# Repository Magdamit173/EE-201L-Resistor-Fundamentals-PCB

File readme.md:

### EE-201L-Resistor-Fundamentals-PCB

- Self Explanatory Repository ~ Cheers!

<br>

<center> <h3> Schematic </h3> </center>

<center> <h3> 3D View </h3> </center>

<center> <h3> Back/Bottom Copper</h3> </center>

<center> <h3> Front/Top Silkscreen</h3> </center>

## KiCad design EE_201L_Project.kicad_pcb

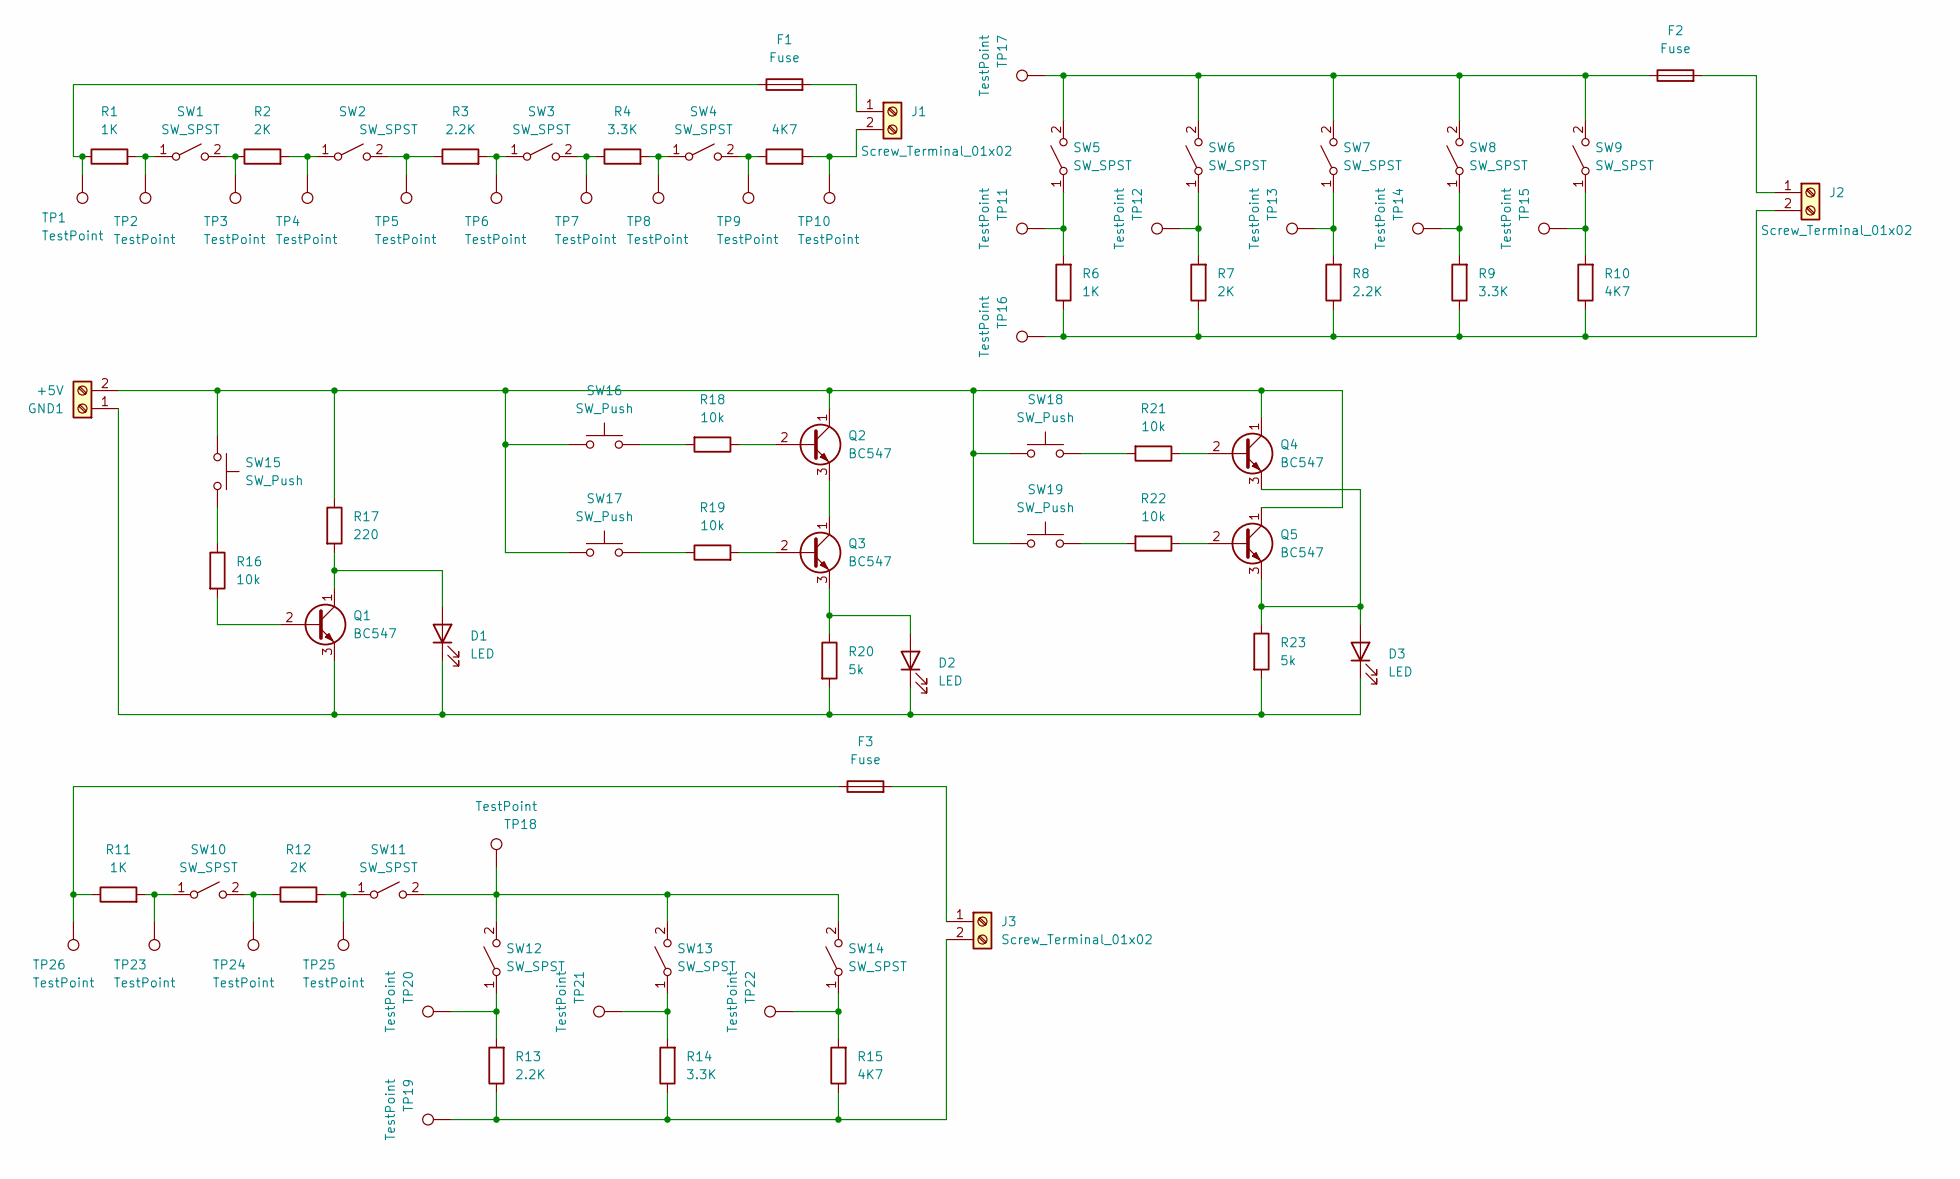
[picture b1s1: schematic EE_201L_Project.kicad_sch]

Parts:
D1, D2, D3: LED; LED_D5.0mm
F1, F2, F3: Fuse; Fuseholder_Cylinder-5x20mm_Schurter_0031_8201_Horizontal_Op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
GND1: +5V; TerminalBlock_Phoenix_MKDS-1,5-2_1x02_P5.00mm_Horizontal
J1, J2, J3: Screw_Terminal_01x02; TerminalBlock_Phoenix_MKDS-1,5-2-5.08_1x02_P5.08mm_Horizont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
Q1, Q2, Q3, Q4, Q5: BC547; TO-92_Inline
R1, R6, R11: 1K; R_Axial_DIN0207_L6.3mm_D2.5mm_P7.62mm_Horizontal_2.00_Diame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
R2, R7, R12: 2K; R_Axial_DIN0207_L6.3mm_D2.5mm_P7.62mm_Horizontal_2.00_Diame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
R3, R8, R13: 2.2K; R_Axial_DIN0207_L6.3mm_D2.5mm_P7.62mm_Horizontal_2.00_Diame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
R4, R9, R14: 3.3K; R_Axial_DIN0207_L6.3mm_D2.5mm_P7.62mm_Horizontal_2.00_Diame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
R5, R10, R15: 4K7; R_Axial_DIN0207_L6.3mm_D2.5mm_P7.62mm_Horizontal_2.00_Diame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
R16, R18, R19, R21, R22: 10k; R_Axial_DIN0207_L6.3mm_D2.5mm_P7.62mm_Horizontal_2.00_Diame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
R17: 220; R_Axial_DIN0207_L6.3mm_D2.5mm_P7.62mm_Horizontal_2.00_Diame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
R20, R23: 5k; R_Axial_DIN0207_L6.3mm_D2.5mm_P7.62mm_Horizontal_2.00_Diame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
SW1, SW2, SW3, SW4, SW5, SW6, SW7, SW8, SW9, SW10, SW11, SW12, SW13, SW14: SW_SPST; SW_CK_JS202011CQN_DPDT_Straight_Enhance
SW15, SW16, SW17, SW18, SW19: SW_Push; SW_PUSH_6mm_H8mm
TP1, TP2, TP3, TP4, TP5, TP6, TP7, TP8, TP9, TP10, TP11, TP12, TP13, TP14, TP15, TP16, TP17, TP18, TP19, TP20, TP21, TP22, TP23, TP24, TP25, TP26: TestPoint; TestPoint_Bridge_Pitch2.54mm_Drill1.0mm

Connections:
unnamed: D1.2 (A), Q1.1 (C), R17.2
unnamed: D1.1 (K), D2.1 (K), D3.1 (K), GND1.1, Q1.3 (E), R20.2, R23.2
unnamed: D2.2 (A), Q3.3 (E), R20.1
unnamed: D3.2 (A), Q4.3 (E), Q5.3 (E), R23.1
unnamed: F1.1, R1.1, TP1.1
unnamed: F3.1, R11.1, TP26.1
unnamed: GND1.2, Q2.1 (C), Q4.1 (C), Q5.1 (C), R17.1, SW15.1, SW16.1, SW17.1, SW18.1, SW19.1
unnamed: F1.2, J1.1
unnamed: J1.2, R5.2, TP10.1
unnamed: F2.2, J2.1
unnamed: J2.2, R6.1, R7.1, R8.1, R9.1, R10.1, TP16.1
unnamed: F3.2, J3.1
unnamed: J3.2, R13.1, R14.1, R15.1, TP19.1
unnamed: Q1.2 (B), R16.2
unnamed: Q2.2 (B), R18.1
unnamed: Q2.3 (E), Q3.1 (C)
unnamed: Q3.2 (B), R19.2
unnamed: Q4.2 (B), R21.1
unnamed: Q5.2 (B), R22.1
unnamed: R16.1, SW15.2
unnamed: R18.2, SW16.2
unnamed: R19.1, SW17.2
unnamed: R21.2, SW18.2
unnamed: R22.2, SW19.2
unnamed: R1.2, SW1.1 (A), TP2.1
unnamed: R2.1, SW1.2 (B), TP3.1
unnamed: R2.2, SW2.1 (A), TP4.1
unnamed: R3.1, SW2.2 (B), TP5.1
unnamed: R3.2, SW3.1 (A), TP6.1
unnamed: R4.1, SW3.2 (B), TP7.1
unnamed: R4.2, SW4.1 (A), TP8.1
unnamed: R5.1, SW4.2 (B), TP9.1
unnamed: R6.2, SW5.1 (A), TP11.1
unnamed: F2.1, SW5.2 (B), SW6.2 (B), SW7.2 (B), SW8.2 (B), SW9.2 (B), TP17.1
unnamed: R7.2, SW6.1 (A), TP12.1
unnamed: R8.2, SW7.1 (A), TP13.1
unnamed: R9.2, SW8.1 (A), TP14.1
unnamed: R10.2, SW9.1 (A), TP15.1
unnamed: R11.2, SW10.1 (A), TP23.1
unnamed: R12.1, SW10.2 (B), TP24.1
unnamed: R12.2, SW11.1 (A), TP25.1
unnamed: SW11.2 (B), SW12.2 (B), SW13.2 (B), SW14.2 (B), TP18.1
unnamed: R13.2, SW12.1 (A), TP20.1
unnamed: R14.2, SW13.1 (A), TP21.1
unnamed: R15.2, SW14.1 (A), TP22.1

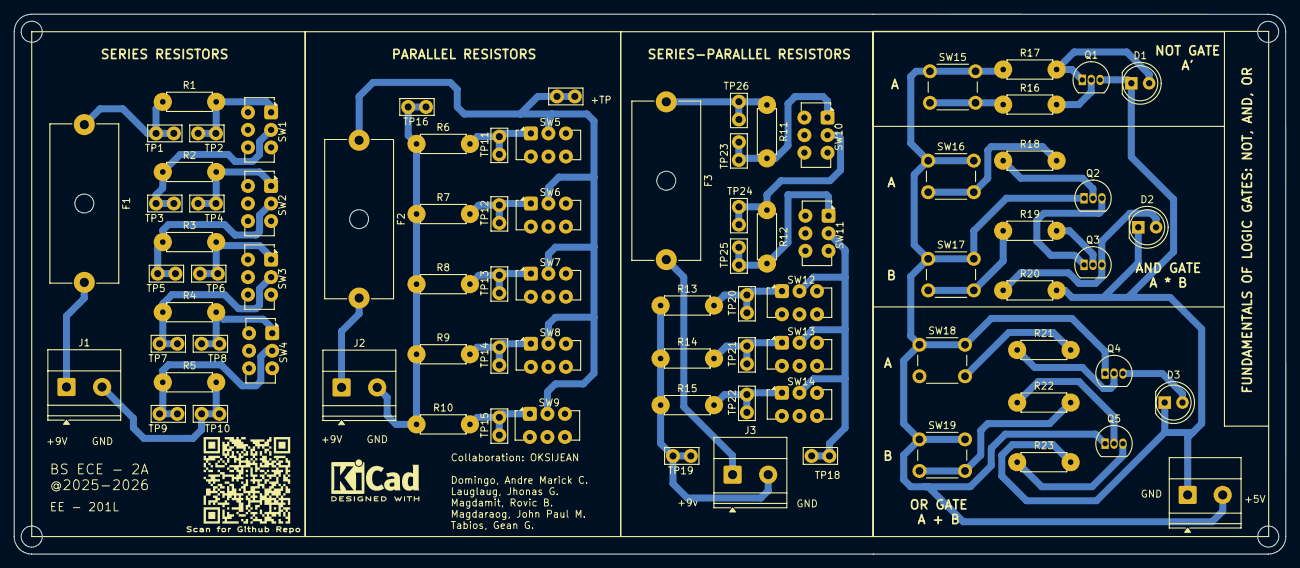
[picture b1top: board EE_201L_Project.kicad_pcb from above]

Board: 2 copper layers, 181.4 x 77.0 mm, 84 parts (0 on the bottom side), 45 nets.

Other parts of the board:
Scan for Github Repo: LOGO; qr_v2

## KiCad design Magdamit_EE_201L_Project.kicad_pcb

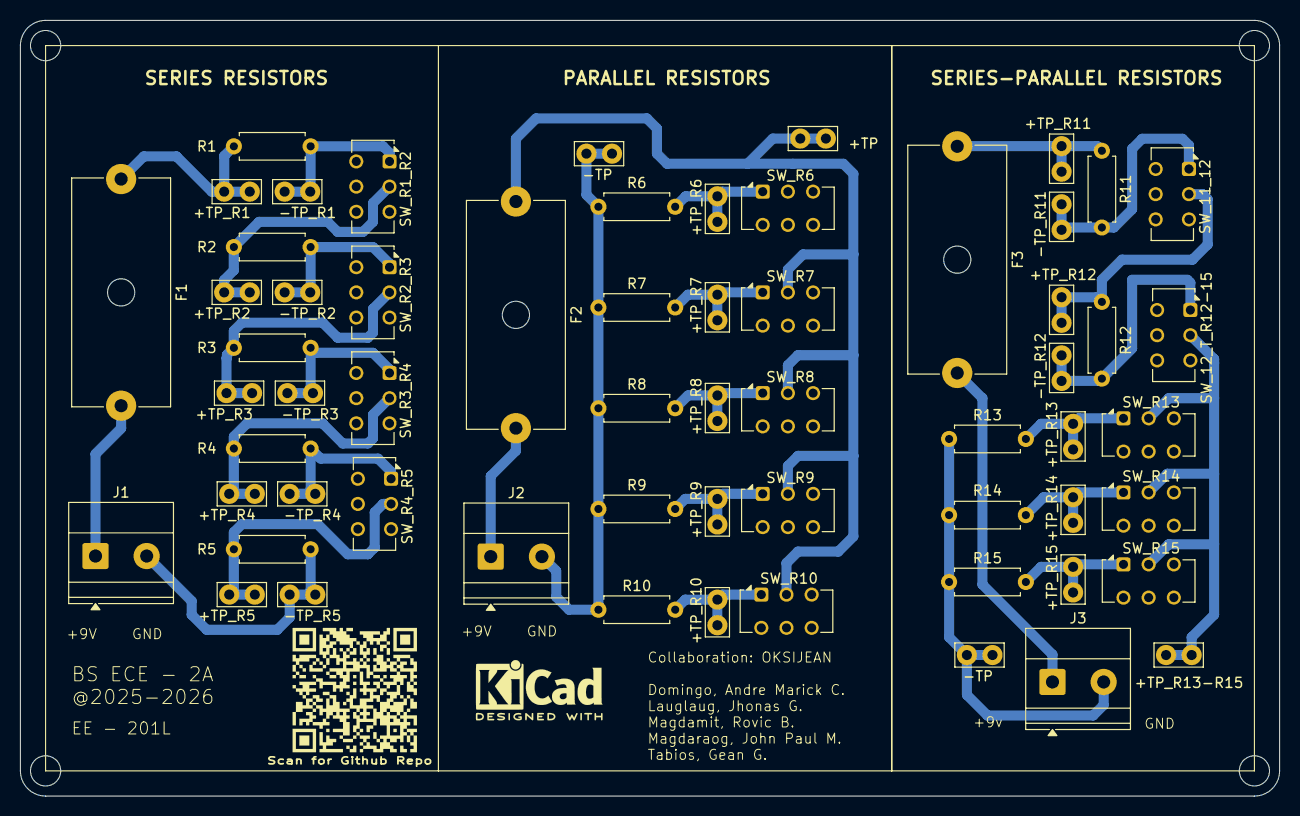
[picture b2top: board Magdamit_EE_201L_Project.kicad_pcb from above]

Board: 2 copper layers, 125.0 x 77.0 mm, 62 parts (0 on the bottom side), 29 nets.

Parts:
+TP_R1, +TP_R2, +TP_R3, +TP_R4, +TP_R5, +TP_R6, +TP_R7, +TP_R8, +TP_R9, +TP_R10, +TP_R11, +TP_R12, +TP_R13, +TP_R13-R15, +TP_R14, +TP_R15: TestPoint; TestPoint_Bridge_Pitch2.54mm_Drill1.0mm
-TP: TestPoint; TestPoint_Bridge_Pitch2.54mm_Drill1.0mm
-TP#2: TestPoint; TestPoint_Bridge_Pitch2.54mm_Drill1.0mm
-TP_R1, -TP_R2, -TP_R3, -TP_R4, -TP_R5, -TP_R11, -TP_R12: TestPoint; TestPoint_Bridge_Pitch2.54mm_Drill1.0mm
F1, F2, F3: Fuse; Fuseholder_Cylinder-5x20mm_Schurter_0031_8201_Horizontal_Op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
J1, J2, J3: Screw_Terminal_01x02; TerminalBlock_Phoenix_MKDS-1,5-2-5.08_1x02_P5.08mm_Horizont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
R1, R6, R11: 330R; R_Axial_DIN0207_L6.3mm_D2.5mm_P7.62mm_Horizontal
R2, R7, R12: 470R; R_Axial_DIN0207_L6.3mm_D2.5mm_P7.62mm_Horizontal
R3, R8, R13: 510R; R_Axial_DIN0207_L6.3mm_D2.5mm_P7.62mm_Horizontal
R4, R9, R14: 1K; R_Axial_DIN0207_L6.3mm_D2.5mm_P7.62mm_Horizontal
R5, R10, R15: 4K7; R_Axial_DIN0207_L6.3mm_D2.5mm_P7.62mm_Horizontal
SW_11_12, SW_12_T_R12-15: SW_SPST; SW_CK_JS202011CQN_DPDT_Straight
SW_R1_R2, SW_R2_R3, SW_R3_R4, SW_R4_R5, SW_R6, SW_R7, SW_R8, SW_R9, SW_R10, SW_R13, SW_R14, SW_R15: SW_SPST; SW_CK_JS202011CQN_DPDT_Straight
Scan for Github Repo: LOGO; qr_v2
TP17: TestPoint; TestPoint_Bridge_Pitch2.54mm_Drill1.0mm

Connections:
unnamed: +TP_R1.1, F1.1, R1.1
unnamed: +TP_R11.1, F3.1, R11.1
unnamed: F1.2, J1.1
unnamed: -TP_R5.1, J1.2, R5.2
unnamed: F2.2, J2.1
unnamed: -TP.1, J2.2, R6.1, R7.1, R8.1, R9.1, R10.1
unnamed: F3.2, J3.1
unnamed: -TP#2.1, J3.2, R13.1, R14.1, R15.1
unnamed: -TP_R1.1, R1.2, SW_R1_R2.1 (A)
unnamed: +TP_R2.1, R2.1, SW_R1_R2.2 (B)
unnamed: -TP_R2.1, R2.2, SW_R2_R3.1 (A)
unnamed: +TP_R3.1, R3.1, SW_R2_R3.2 (B)
unnamed: -TP_R3.1, R3.2, SW_R3_R4.1 (A)
unnamed: +TP_R4.1, R4.1, SW_R3_R4.2 (B)
unnamed: -TP_R4.1, R4.2, SW_R4_R5.1 (A)
unnamed: +TP_R5.1, R5.1, SW_R4_R5.2 (B)
unnamed: +TP_R6.1, R6.2, SW_R6.1 (A)
unnamed: F2.1, SW_R6.2 (B), SW_R7.2 (B), SW_R8.2 (B), SW_R9.2 (B), SW_R10.2 (B), TP17.1
unnamed: +TP_R7.1, R7.2, SW_R7.1 (A)
unnamed: +TP_R8.1, R8.2, SW_R8.1 (A)
unnamed: +TP_R9.1, R9.2, SW_R9.1 (A)
unnamed: +TP_R10.1, R10.2, SW_R10.1 (A)
unnamed: -TP_R11.1, R11.2, SW_11_12.1 (A)
unnamed: +TP_R12.1, R12.1, SW_11_12.2 (B)
unnamed: -TP_R12.1, R12.2, SW_12_T_R12-15.1 (A)
unnamed: +TP_R13-R15.1, SW_12_T_R12-15.2 (B), SW_R13.2 (B), SW_R14.2 (B), SW_R15.2 (B)
unnamed: +TP_R13.1, R13.2, SW_R13.1 (A)
unnamed: +TP_R14.1, R14.2, SW_R14.1 (A)
unnamed: +TP_R15.1, R15.2, SW_R15.1 (A)

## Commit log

2025-08-30 8.31.2025
2025-08-30 8.31.2025 added schematic
2025-08-31 9.1.2025
2025-10-01 10.1.2025
2025-10-04 10.4.2025
2025-10-04 10.4.2025 --0
2025-10-04 10.4.2025 --1
2025-10-05 10.5.2025
2025-10-22 10.22.2025
2025-10-22 10.22.2025 --fixed
